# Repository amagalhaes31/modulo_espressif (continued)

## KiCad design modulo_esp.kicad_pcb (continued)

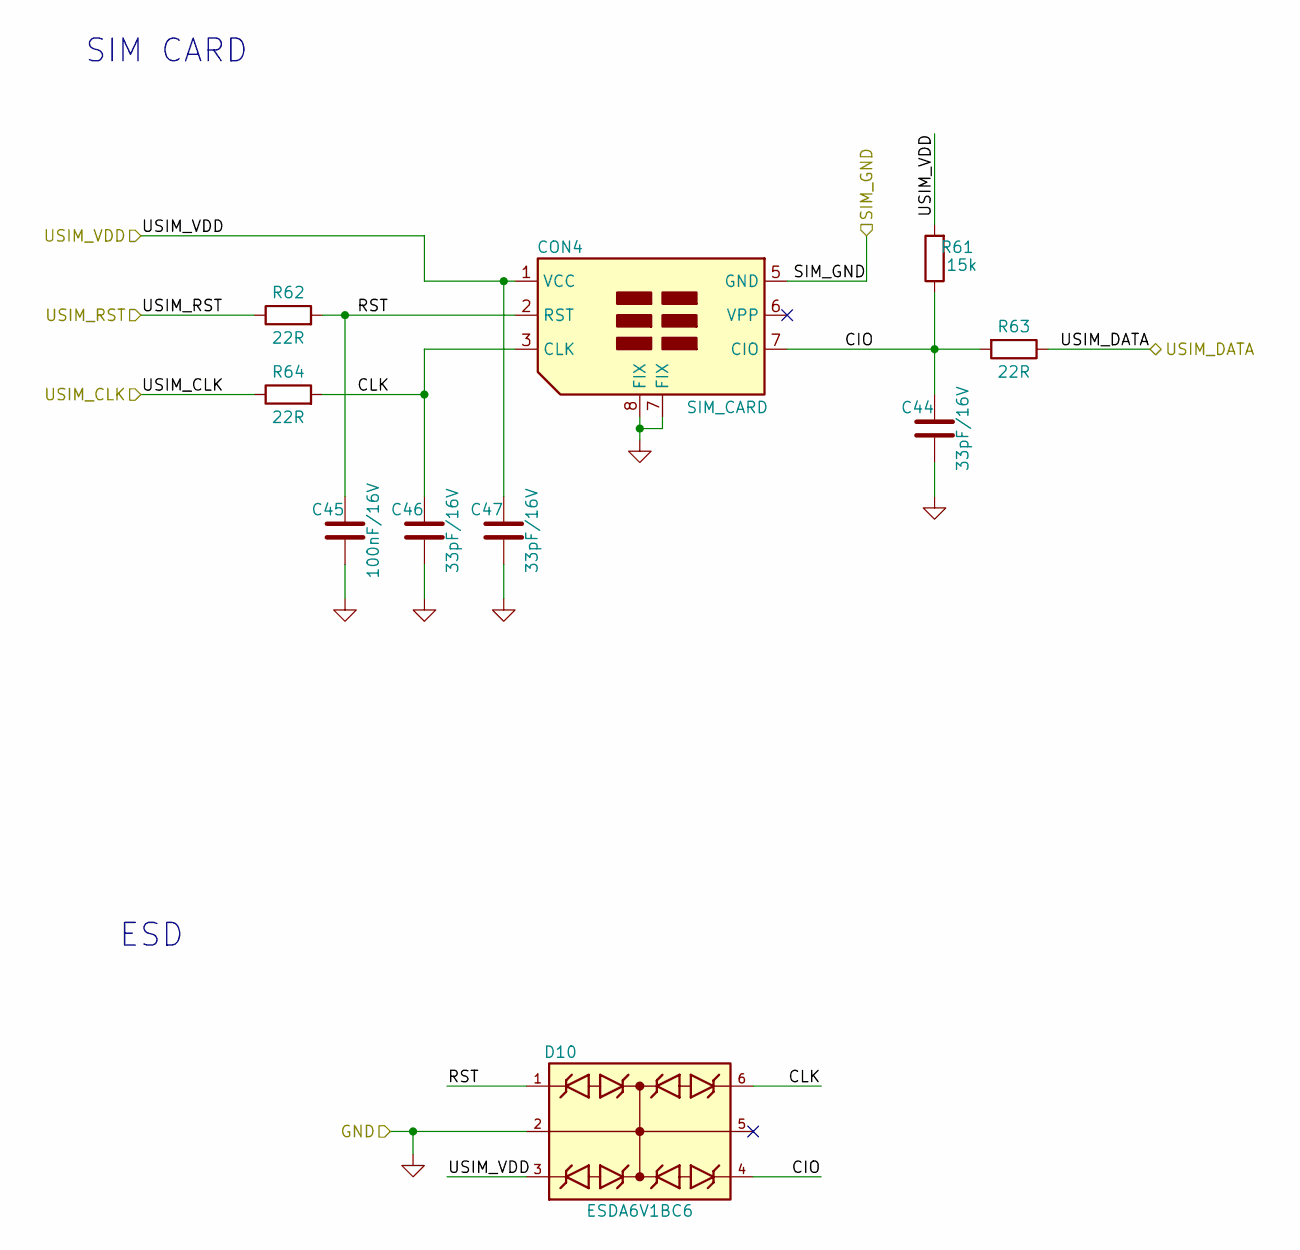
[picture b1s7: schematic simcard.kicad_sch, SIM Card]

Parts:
C44, C46, C47: 33pF/16V; C_0603_1608Metric_Pad1.08x0.95mm_HandSolder
C45: 100nF/16V; C_0603_1608Metric_Pad1.08x0.95mm_HandSolder
CON4: SIM_CARD; SIM_CARD_SIMPLES
D10: ESDA6V1BC6; PARTREV 2
R61: 15k; R_0603_1608Metric_Pad0.98x0.95mm_HandSolder
R62, R63, R64: 22R; R_0603_1608Metric_Pad0.98x0.95mm_HandSolder

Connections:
/BG95M3/SIM_CARD/CLK: C46.2, CON4.3 (CLK), D10.6, R64.2
/BG95M3/SIM_CARD/RST: C45.2, CON4.2 (RST), D10.1, R62.2
/BG95M3/USIM_CLK: R64.1; also elsewhere on the board
/BG95M3/USIM_DATA: R63.1; also elsewhere on the board
/BG95M3/USIM_GND: CON4.5 (GND); also elsewhere on the board
/BG95M3/USIM_RST: R62.1; also elsewhere on the board
/BG95M3/USIM_VDD: C47.2, CON4.1 (VCC), D10.3, R61.2; also elsewhere on the board

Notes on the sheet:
ESD
SIM CARD

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
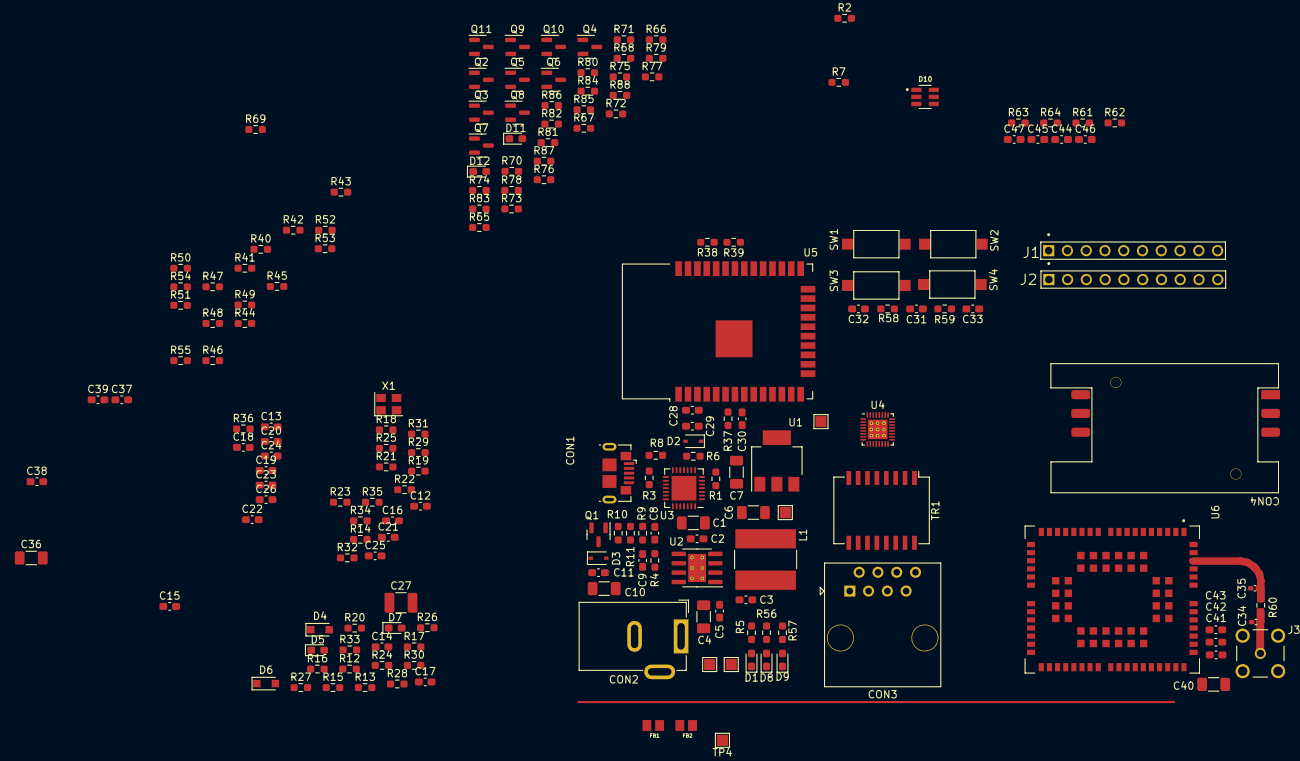
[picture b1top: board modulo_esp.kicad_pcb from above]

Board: 2 copper layers, 185 parts (0 on the bottom side), 144 nets.

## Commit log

2022-06-19 Updated Readme.
2022-06-22 Adicionado o esquema elétrico com a fonte de alimentacao.
2022-06-24 Adicionado o circuito USB-Serial para gravar ESP32
2022-06-28 Adicionado o sheet do PHY IP101
2022-06-28 Organizando os nomes dos arquivos
2022-06-28 Adicionado IP101
2022-06-28 Renomeado POWER_SUPPLU para power_supply
2022-06-28 Renomeado PHY_IP101 para phy_ip101.
2022-07-03 Organizado a folha da power supply
2022-07-03 Atualizado o arquivo .gitignore
2022-07-05 Iniciando o circuito do PHY Ethernet
2022-07-05 Continuando o circuito do PHY Ethernet
2022-07-06 Continuando com o projeto do circuito do PHY Ethernet
2022-07-06 Concluido o circuito do PHY ETH
2022-07-07 Iniciando o circuito do conector RJ45
2022-07-09 Criado um sheet para circuito do ESP32
2022-07-09 Adicionado o circuito de entrada do PHY ETH
2022-07-19 Adicionado BG95-M3 e TVS do PHY Ethernet
2022-07-27 Adicionado o circuito de alimentação e reset do BG95
2022-07-27 Circuito de Reset e Serial TxD do módulo BG95
2022-07-27 Adicionado os circuitos de RxD, NEt Status, Status do módulo BG95
2022-07-30 Adicionado regulador 3.3V
2022-07-31 Inserido o circuito do SIm Card
2022-08-02 Adicionado hierarchical label
2022-08-03 Cont. hierarchical label e descrição das folhas
2022-08-03 Interligando as hierarquias
2022-08-03 Inserido ferrite bead para cada sheet
2022-08-05 Continuando a adição dos hierarchical labels
2022-08-05 Inserido encapsulamento 0603 para os resistores
2022-08-05 Adicionado footprint para AP6503 (U2)
2022-08-06 Corrigido alguns ERC e adicionado circuito DTR e RI do BG95
2022-08-06 Correções de ECR-Electrical Rules Checker
2022-08-06 Corrigido todos os ERC
2022-08-06 Adicionado duas barras de pinos 1x10
2022-08-06 Organização do sheet esp32
2022-08-09 Corrigido a net do ~{PWRKEY}
2022-08-09 Criado um sheet para o SIM Card
2022-08-09 Criado um sheet para os periféricos do módulo IoT
2022-08-09 Atualização das referências dos componentes
2022-08-09 Corrigido hierarchical label +3.3V do Módulo IoT
2022-08-10 Inserido as informações dos sheets do modulo IoT
2022-08-11 Inserido um pino de controle de reset do PHY
2022-08-11 Organizado o sheet do PHY ETH
2022-08-11 Criado o arquivo pcb
2022-08-11 Referencia dos componentes
2022-08-14 Inserido proteção ESD no SIM Card
2022-08-16 Capacitores com encapsulamento 0603
2022-08-16 Adicionado os pads dos Test Point e alterado o Bead
2022-08-16 Iniciando a posicionar os componentes no PCB
2022-08-31 Continuando com o desenvolvimento do layout
